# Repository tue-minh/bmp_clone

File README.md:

# 🔧 BMP Clone & TUE CMSIS-DAP Programmer / Debugger

This repository contains the KiCad hardware, firmware, and host software for two STM32 debug probe implementations:

1. **`stm32f401rct6_stlink/` (Latest - v1.0.1):** **CMSIS-DAP Programmer & Debugger + Virtual COM Port** probe based on **STM32F401RCT6**, paired with a lightweight **native C++17 GUI** for **Windows** and **Ubuntu**.
2. **`blackmagic-firmware-v1.10.2/` & `hardware/`:** **Black Magic Probe (BMP)** clone based on **STM32F103C8T6 (Bluepill)**.

---

## 📁 Repository Structure

| Folder / File | Description |
| :--- | :--- |
| [`stm32f401rct6_stlink/`](stm32f401rct6_stlink/firmware/README.md) | STM32F401RCT6 probe project (KiCad PCB + CMSIS-DAP/VCP Firmware + C++ GUI) |
| [`stm32f401rct6_stlink/firmware/`](stm32f401rct6_stlink/firmware/README.md) | STM32F401RCT6 firmware source & prebuilt `.bin`/`.hex` (`tue-cmsis-dap-stm32f401rct6.bin`) |
| [`stm32f401rct6_stlink/gui/`](stm32f401rct6_stlink/gui/main_gui.cpp) | Native C++17 GUI for Windows (`TUE_CMSIS_DAP_CPP.exe`) |
| [`stm32f401rct6_stlink/gui/linux/`](stm32f401rct6_stlink/gui/linux/linux_main.cpp) | Native C++17 Qt5 GUI & `.deb` package for Ubuntu (`tue-cmsis-dap_1.0.1_amd64.deb`) |
| `blackmagic-firmware-v1.10.2/` | Black Magic Probe v1.10.2 firmware for STM32F103C8T6 |
| `hardware/` & `Tue_BMP_Gerber/` | KiCad hardware design & Gerber files for the Bluepill BMP |

---

## 🚀 Part 1: TUE CMSIS-DAP (STM32F401RCT6 - Recommended)

### ✨ Key Features
* **USB Composite (`VID=0x0483`, `PID=0x5752`):**
  * **Interface 0:** `CMSIS-DAP v1.10` HID (compatible with OpenOCD, pyOCD, Keil MDK, STM32CubeIDE, Probe-rs).
  * **Interface 1 & 2:** `USB Serial Device (VCP)` bridged directly to `USART1` (`PA9` TX / `PB7` RX).
* **Industrial Status LED (`PC13`):**
  * *Single Blink (1.0s):* Idle / Standby (not connected).
  * *Double Blink (1.2s):* Target SWD Connected.
  * *Solid ON:* Debug Mode active (blinks **3 times** cleanly when executing a debug command, then returns to Solid ON).
  * *Rapid Continuous Flicker (12.5 Hz):* Active non-debug target operation (Flashing / Erasing / Verifying / Reset / Memory R/W) until completed.
  * *3 Fast Blinks (Error):* SWD Error / Verify Mismatch.
* **Hardware Reset Button (`PA0`):** Press and hold to pull `PB8` (`nRESET`) to `0V`; release to return to `3.3V` immediately (non-blocking).
* **Lightweight Native C++17 GUI (`stm32f401rct6_stlink/gui/`):**
  * Automatic USB Plug & Play detection (HID + COM).
  * Direct `.bin`, `.hex`, and `.elf` flashing/verifying/mass-erasing for **STM32F1 / F3 / F4 / G4 / L4** without OpenOCD, or toggle **`Use OpenOCD`** + GDB Server (`:3333`).
  * Clicking **Connect** reads the chip name, IDs, Flash size, RDP, UID, and the first 512 bytes of on-chip Flash; includes **Disconnect**, **HW Reset** / **SWD Reset**, and a dedicated **CPU Debug Window** (`Start Debug`, `Exit Debug`, `Halt`, `Run`, `Step Into`, `Step Out`, `Read Regs`).
  * 9 SWD clock speeds (`4 MHz` – `20 kHz`), **Memory Hex Viewer & Mem32**, and **UART Terminal** (`Echo TX`, auto-clear input, selectable `\r`, `\n`, `\t`, and `Parse \r \n \t \xHH`).

### 📦 Quick Download & Install (Prebuilt Files in Folders)
* **STM32F401RCT6 Firmware:** Flash `stm32f401rct6_stlink/firmware/tue-cmsis-dap-stm32f401rct6.bin` (or `.hex`) at `0x08000000` (via DFU or ST-Link).
* **Windows:** Run `stm32f401rct6_stlink/gui/TUE_CMSIS_DAP_CPP.exe` directly.
* **Ubuntu / Linux:**
  ```bash
  sudo apt install ./stm32f401rct6_stlink/gui/linux/tue-cmsis-dap_1.0.1_amd64.deb
  tue-cmsis-dap
  ```
  *(Or run the standalone binary `stm32f401rct6_stlink/gui/linux/tue-cmsis-dap-ubuntu-x86_64`)*
* For detailed firmware & GUI build instructions, see [`stm32f401rct6_stlink/firmware/README.md`](stm32f401rct6_stlink/firmware/README.md).

---

## 🔧 Phần 2: Black Magic Probe trên STM32F103C8T6 (Bluepill)

This guide provides detailed instructions for loading Blackmagic firmware onto the Bluepill board using either an ST-Link or Black Magic Probe (BMP).

<table align="center">
  <tr>
    <th>Front</th>
    <th>Back</th>
  </tr>
  <tr>
    <td></td>
    <td></td>
  </tr>
</table>

### 📂 1. Prepare the Firmware Files
Locate the following files in your build directory:
- `.../blackmagic-firmware-v1.10.2/bluepill/blackmagic_dfu-bluepill.elf`
- `.../blackmagic-firmware-v1.10.2/bluepill/blackmagic-bluepill.elf`

### 🛠️ 2. Install GDB Tool
Open **PowerShell** or **Terminal** and run:
```bash
arm-none-eabi-gdb
```

### ⚡ 3. Flash the Firmware

#### 🔹 Method A: Using ST-LINK
```bash
# Erase old memory
st-flash erase

# Flash the DFU Bootloader (at address 0x8000000)
st-flash --flash=0x20000 write .../blackmagic-firmware-v1.10.2/bluepill/blackmagic_dfu-bluepill.elf 0x8000000

# Flash the main firmware (at address 0x8002000) and reset
st-flash --flash=0x20000 --reset write .../blackmagic-firmware-v1.10.2/bluepill/blackmagic-bluepill.elf 0x8002000
```

#### 🔹 Method B: Using Black Magic Probe (BMP)
```bash
target extended-remote \\.\COMx           # For Windows
target extended-remote /dev/tty*          # For Linux

monitor swdp_scan
attach 1
monitor halt
monitor erase_mass

file .../blackmagic-firmware-v1.10.2/bluepill/blackmagic_dfu-bluepill.elf
load

file .../blackmagic-firmware-v1.10.2/bluepill/blackmagic-bluepill.elf
load

monitor reset
continue
```

### 🧠 Important Notes & Troubleshooting
- STM32F103 Flash starts at `0x08000000` (DFU Bootloader occupies `0x08000000 → 0x08002000`).
- After flashing, reconnect via USB to see **GDB Port** and **UART Port**.

| **Error** | **Cause** | **Solution** |
| :--- | :--- | :--- |
| `unknown architecture "arm"` | Incorrect GDB version | Use `arm-none-eabi-gdb`. |
| `load failed` | Memory not erased | Run `monitor erase_mass` before loading. |
| `attach` error | Physical connection issue | Check `monitor swdp_scan`. |
| Target not detected | Loose or incorrect SWD wires | Verify SWDIO and SWCLK connections. |

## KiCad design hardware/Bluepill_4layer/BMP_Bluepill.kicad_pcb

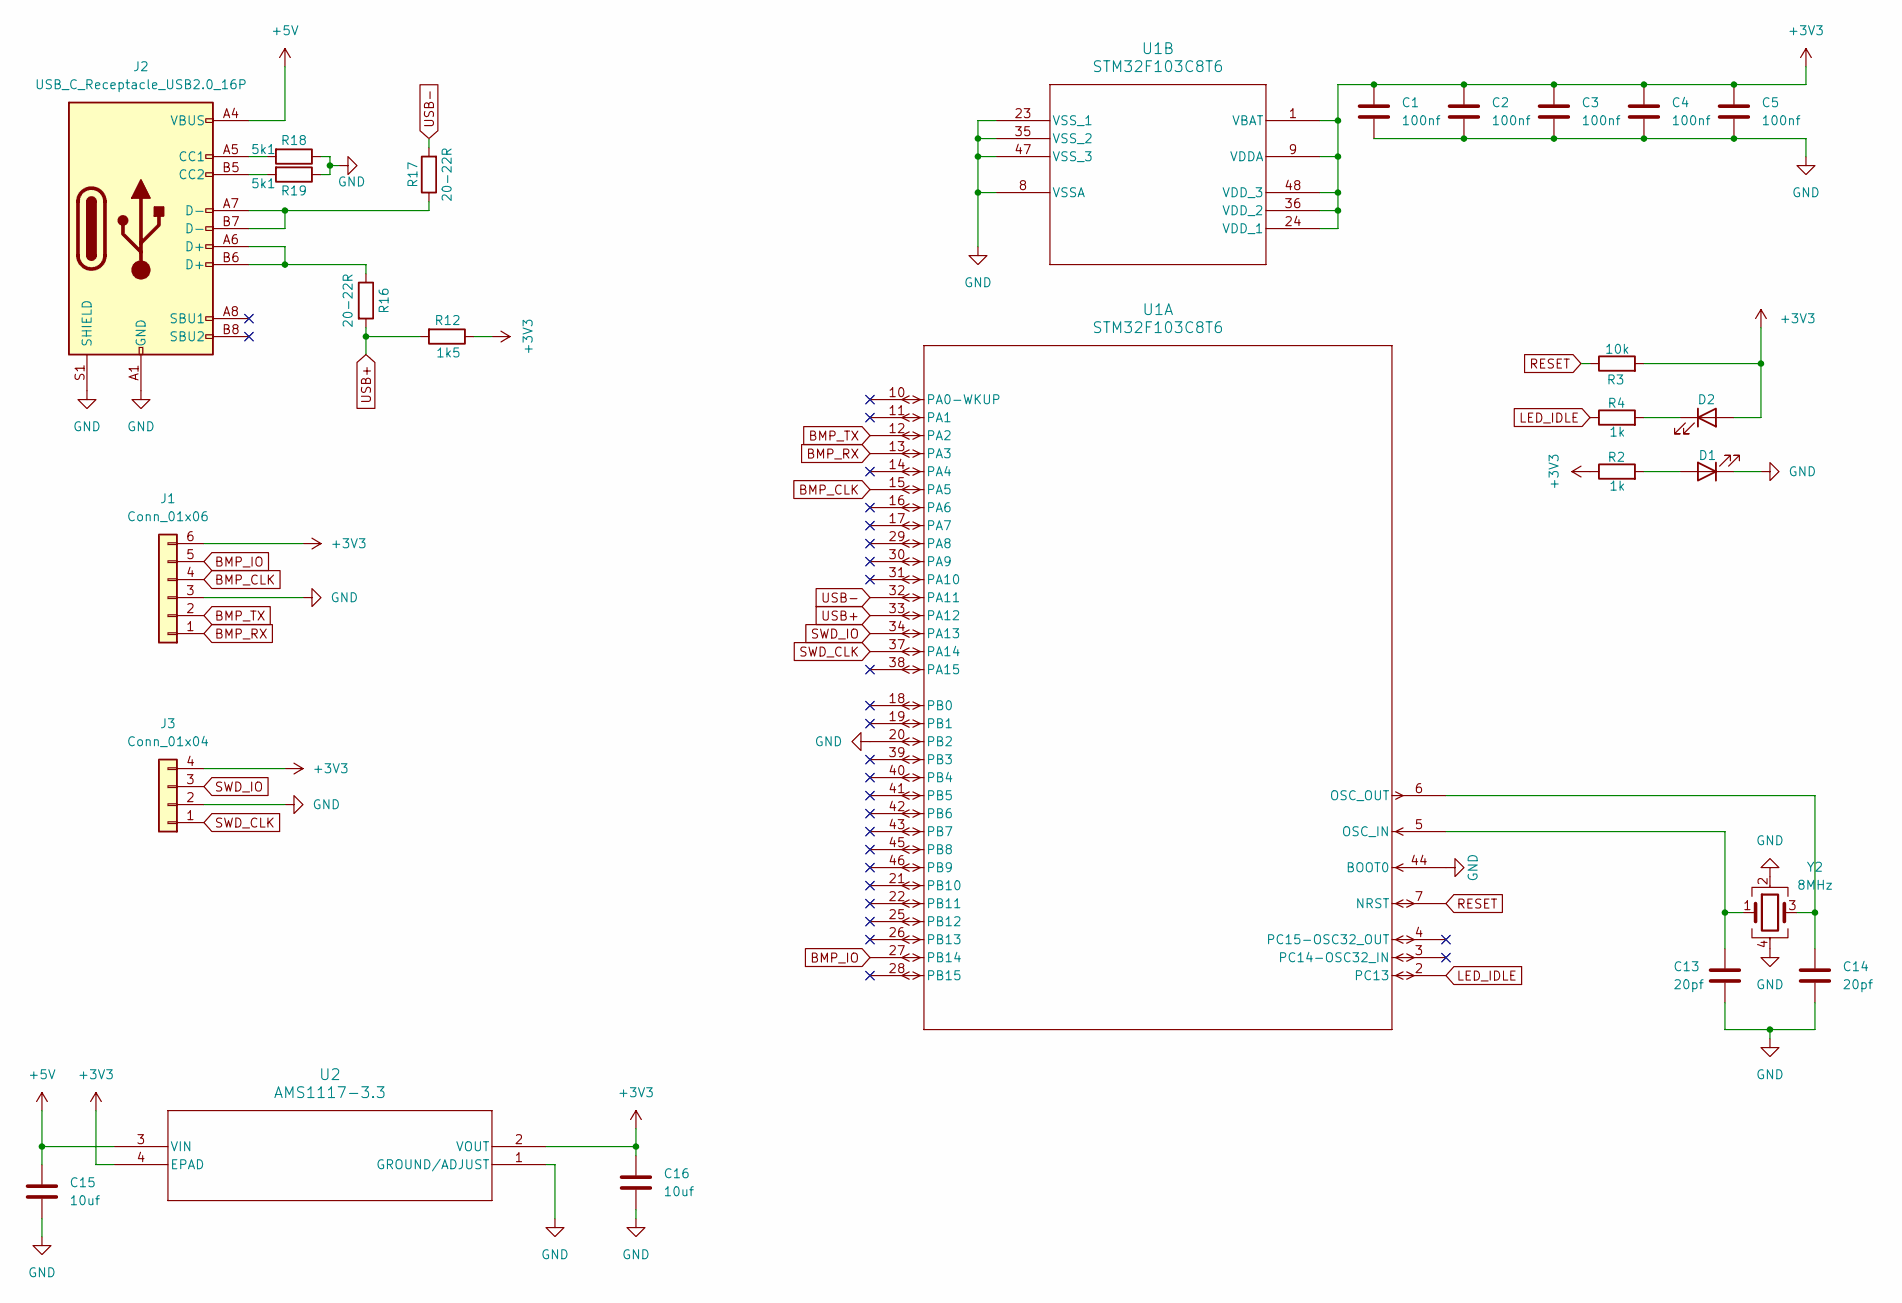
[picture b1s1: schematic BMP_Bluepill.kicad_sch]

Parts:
C1, C2, C3, C4, C5: 100nf; C_0603_1608Metric_Pad1.08x0.95mm_HandSolder
C13, C14: 20pf; C_0603_1608Metric_Pad1.08x0.95mm_HandSolder
C15, C16: 10uf; C_0603_1608Metric_Pad1.08x0.95mm_HandSolder
D1, D2: LED; LED_0603_1608Metric_Pad1.05x0.95mm_HandSolder
J1: Conn_01x06; JST_XH_B6B-XH-A_1x06_P2.50mm_Vertical
J2: USB_C_Receptacle_USB2.0_16P; USB_C_Receptacle_GCT_USB4105-xx-A_16P_TopMnt_Horizontal
J3: Conn_01x04; PinSocket_1x04_P2.54mm_Vertical
R2, R4: 1k; R_0603_1608Metric_Pad0.98x0.95mm_HandSolder
R3: 10k; R_0603_1608Metric_Pad0.98x0.95mm_HandSolder
R12: 1k5; R_0603_1608Metric_Pad0.98x0.95mm_HandSolder
R16, R17: 20-22R; R_0603_1608Metric_Pad0.98x0.95mm_HandSolder
R18, R19: 5k1; R_0603_1608Metric_Pad0.98x0.95mm_HandSolder
U1: STM32F103C8T6; LQFP48_STM
U2: AMS1117-3.3; SOT_AMS_ADS
Y2: 8MHz; Crystal_SMD_5032-4Pin_5.0x3.2mm

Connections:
+3V3: C1.1, C2.1, C3.1, C4.1, C5.1, C16.1, D2.2 (A), J1.6, J3.4, R2.1, R3.2, R12.1, U1.1 (VBAT), U1.9 (VDDA), U1.24 (VDD_1), U1.36 (VDD_2), U1.48 (VDD_3), U2.2 (VOUT), U2.4 (EPAD)
+5V: C15.1, J2.A4 (VBUS), J2.A9 (VBUS), J2.B4 (VBUS), J2.B9 (VBUS), U2.3 (VIN)
BMP_CLK: J1.4, U1.15 (PA5)
BMP_IO: J1.5, U1.27 (PB14)
BMP_RX: J1.1, U1.13 (PA3)
BMP_TX: J1.2, U1.12 (PA2)
GND: C1.2, C2.2, C3.2, C4.2, C5.2, C13.2, C14.2, C15.2, C16.2, D1.1 (K), J1.3, J2.A1 (GND), J2.A12 (GND), J2.B1 (GND), J2.B12 (GND), J2.S1 (SHIELD), J3.2, R18.1, R19.1, U1.8 (VSSA), U1.20 (PB2), U1.23 (VSS_1), U1.35 (VSS_2), U1.44 (BOOT0), U1.47 (VSS_3), U2.1 (GROUND/ADJUST), Y2.2, Y2.4
LED_IDLE: R4.1, U1.2 (PC13)
unnamed: D1.2 (A), R2.2
unnamed: D2.1 (K), R4.2
unnamed: J2.A5 (CC1), R18.2
unnamed: J2.B5 (CC2), R19.2
unnamed: J2.A6 (D+), J2.B6 (D+), R16.1
unnamed: J2.A7 (D-), J2.B7 (D-), R17.1
unnamed: C13.1, U1.5 (OSC_IN), Y2.1
unnamed: C14.1, U1.6 (OSC_OUT), Y2.3
RESET: R3.1, U1.7 (NRST)
SWD_CLK: J3.1, U1.37 (PA14)
SWD_IO: J3.3, U1.34 (PA13)
USB+: R12.2, R16.2, U1.33 (PA12)
USB-: R17.2, U1.32 (PA11)

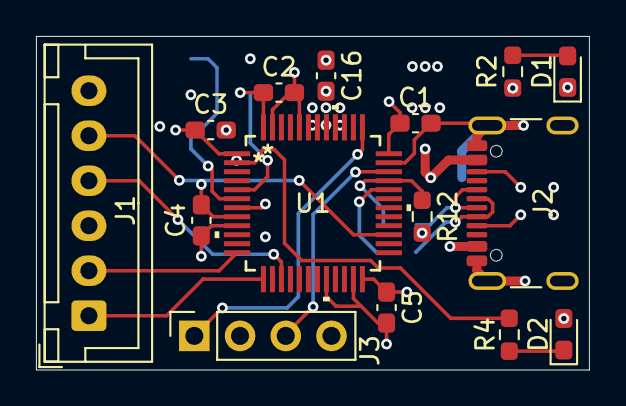
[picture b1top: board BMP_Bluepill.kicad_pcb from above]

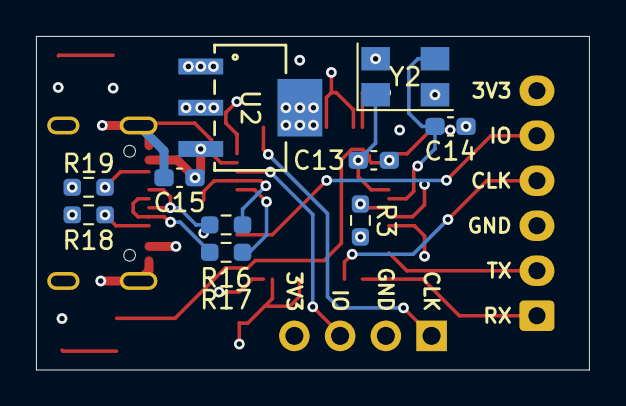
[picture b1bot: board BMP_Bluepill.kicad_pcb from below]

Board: 4 copper layers, 30.7 x 18.5 mm, 25 parts (10 on the bottom side), 21 nets.

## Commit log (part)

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2026-03-03 fix layout
2026-03-28 add markdown, add firmware file
2026-03-28 clear trash file
2026-03-29 update README image
2026-03-29 relocate file
2026-05-01 update layout
2026-05-04 add 4 layers pcb version
